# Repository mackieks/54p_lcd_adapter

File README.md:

simple flex adapter for connecting a 54-pin 3.5" 640x480 LCD to a standard 40-pin LCD ZIF connector. Order 0.12mm thickness (0.5oz Cu) with 0.2mm PI stiffener. `stiffener.gbr` shows the size and location of the stiffener. 

[GoldPhoenix FPC pool](https://www.goldphoenixpcb.com/fpc-pool.html) is my recommended vendor. JLCPCB also works.

ZIF connector is Molex 51296-5494.

Design from 2019

## License
Solderpad Hardware License v2.1

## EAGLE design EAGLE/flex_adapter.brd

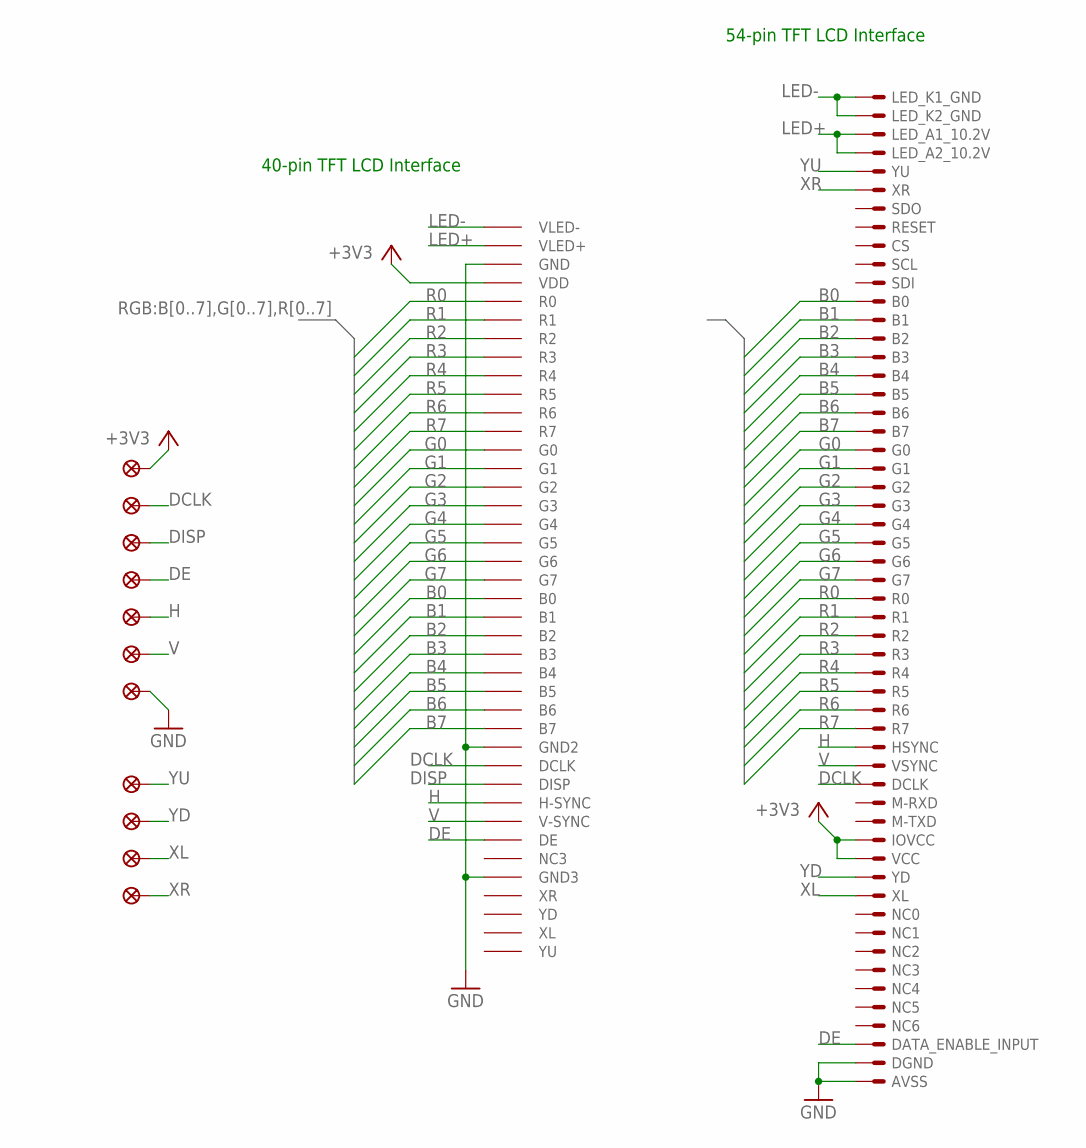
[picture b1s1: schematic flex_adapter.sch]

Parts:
U$1: 51296-5494; 51296
U$2: 40PIN
U$3, U$4, U$5, U$6, U$7, U$8, U$9, U$10, U$11, U$12, U$13: TESTPAD; SOLDERPAD

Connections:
+3V3: U$1.41 (IOVCC), U$1.42 (VCC), U$2.P$4 (VDD), U$4.P$1
B0: U$1.12 (B0), U$2.P$21 (B0)
B1: U$1.13 (B1), U$2.P$22 (B1)
B2: U$1.14 (B2), U$2.P$23 (B2)
B3: U$1.15 (B3), U$2.P$24 (B3)
B4: U$1.16 (B4), U$2.P$25 (B4)
B5: U$1.17 (B5), U$2.P$26 (B5)
B6: U$1.18 (B6), U$2.P$27 (B6)
B7: U$1.19 (B7), U$2.P$28 (B7)
DCLK: U$1.38 (DCLK), U$2.P$30 (DCLK), U$8.P$1
DE: U$1.52 (DATA_ENABLE_INPUT), U$2.P$34 (DE), U$6.P$1
DISP: U$2.P$31 (DISP), U$7.P$1
G0: U$1.20 (G0), U$2.P$13 (G0)
G1: U$1.21 (G1), U$2.P$14 (G1)
G2: U$1.22 (G2), U$2.P$15 (G2)
G3: U$1.23 (G3), U$2.P$16 (G3)
G4: U$1.24 (G4), U$2.P$17 (G4)
G5: U$1.25 (G5), U$2.P$18 (G5)
G6: U$1.26 (G6), U$2.P$19 (G6)
G7: U$1.27 (G7), U$2.P$20 (G7)
GND: U$1.53 (DGND), U$1.54 (AVSS), U$2.P$3 (GND), U$2.P$29 (GND2), U$2.P$36 (GND3), U$9.P$1
H: U$1.36 (HSYNC), U$2.P$32 (H-SYNC), U$5.P$1
LED+: U$1.3 (LED_A1_10.2V), U$1.4 (LED_A2_10.2V), U$2.P$2 (VLED+)
LED-: U$1.1 (LED_K1_GND), U$1.2 (LED_K2_GND), U$2.P$1 (VLED-)
R0: U$1.28 (R0), U$2.P$5 (R0)
R1: U$1.29 (R1), U$2.P$6 (R1)
R2: U$1.30 (R2), U$2.P$7 (R2)
R3: U$1.31 (R3), U$2.P$8 (R3)
R4: U$1.32 (R4), U$2.P$9 (R4)
R5: U$1.33 (R5), U$2.P$10 (R5)
R6: U$1.34 (R6), U$2.P$11 (R6)
R7: U$1.35 (R7), U$2.P$12 (R7)
V: U$1.37 (VSYNC), U$2.P$33 (V-SYNC), U$3.P$1
XL: U$1.44 (XL), U$12.P$1
XR: U$1.6 (XR), U$13.P$1
YD: U$1.43 (YD), U$11.P$1
YU: U$1.5 (YU), U$10.P$1

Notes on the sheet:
40-pin TFT LCD Interface
54-pin TFT LCD Interface

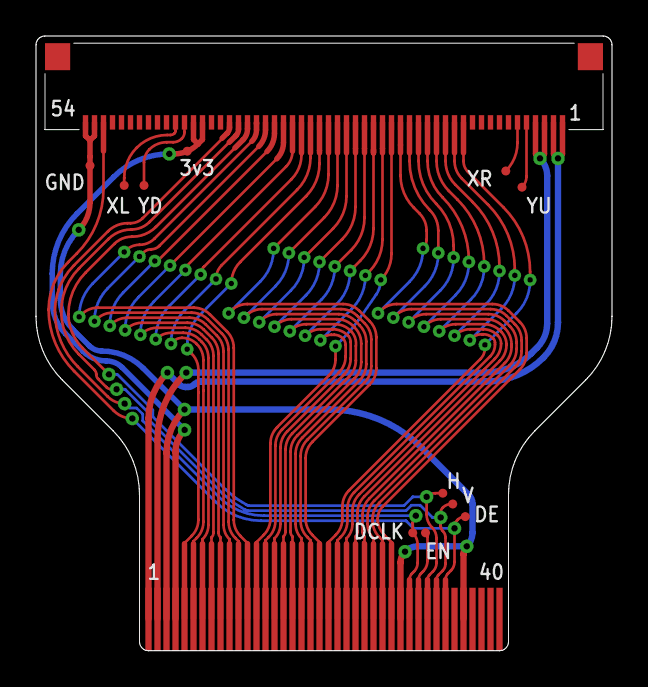
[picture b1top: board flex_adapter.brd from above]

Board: 2 copper layers, 32.0 x 34.1 mm, 13 parts (0 on the bottom side), 37 nets.

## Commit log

2024-07-05 Add files
2024-07-05 fix image
